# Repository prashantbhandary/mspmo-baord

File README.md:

# MSPM0G3507 Development Board

A compact USB-C development board for TI's **MSPM0G3507** (Arm Cortex-M0+,
80 MHz, 128 KB flash, 32 KB SRAM), with an on-board USB-to-UART bridge, a
3-axis accelerometer and a Tag-Connect SWD footprint.

Full write-up: <https://bhandari-prashant.com.np/projects/mspm0-board>

## At a glance

| | |
| --- | --- |
| Size | 53 × 28 mm, 2-layer, 1.6 mm FR-4, 4 × M3 holes, fiducials |
| Power | USB-C (5.1 kΩ CC pull-downs) → SPX3819 3.3 V LDO |
| USB | CH340E USB-UART on UART0, with RTS/CTS; USBLC6-2SC6 ESD protection |
| Sensor | LIS2DH accelerometer on I²C0, INT1/INT2 to the MCU |
| Clock | 8 MHz crystal on HFXIN/HFXOUT; 100 kΩ on ROSC |
| Debug | SWD + NRST on a TC2030 Tag-Connect footprint (no header) |

## MCU pin map

| Signal | MSPM0 pin | Goes to |
| --- | --- | --- |
| UART0 TX / RX | PA0 / PA1 | CH340E RXD / TXD |
| UART0 RTS / CTS | PA8 / PA9 | CH340E CTS / RTS |
| I²C0 SDA / SCL | PA10 / PA11 | LIS2DH |
| INT1 / INT2 | PB8 / PB9 | LIS2DH interrupts |
| SWDIO / SWCLK | PA19 / PA20 | TC2030 |
| HFXIN / HFXOUT | PA5 / PA6 | 8 MHz crystal |
| ROSC | PA2 | 100 kΩ to GND |

## Project files

```
mspmo-baord/
├── mspmo-baord.kicad_pro   open this in KiCad
├── mspmo-baord.kicad_sch   schematic
├── mspmo-baord.kicad_pcb   layout
├── MSPM0.kicad_sym         custom MCU symbol (referenced by sym-lib-table)
├── bom/ibom.html           interactive BOM, open in a browser
├── fab/
│   ├── mfr/                Gerbers + drill files
│   ├── mspmo-baord.csv     BOM with LCSC part numbers
│   └── posfile/            pick-and-place positions
├── mfr.zip                 fab/mfr zipped for upload
└── images/                 renders used in this README
```

## Ordering

Upload `mfr.zip` to the board house. For assembly, use `fab/mspmo-baord.csv`
(BOM) and `fab/posfile/mspmo-baord-all-pos.csv` (CPL).

## Tools

KiCad 10. Renders made with `kicad-cli pcb render`.

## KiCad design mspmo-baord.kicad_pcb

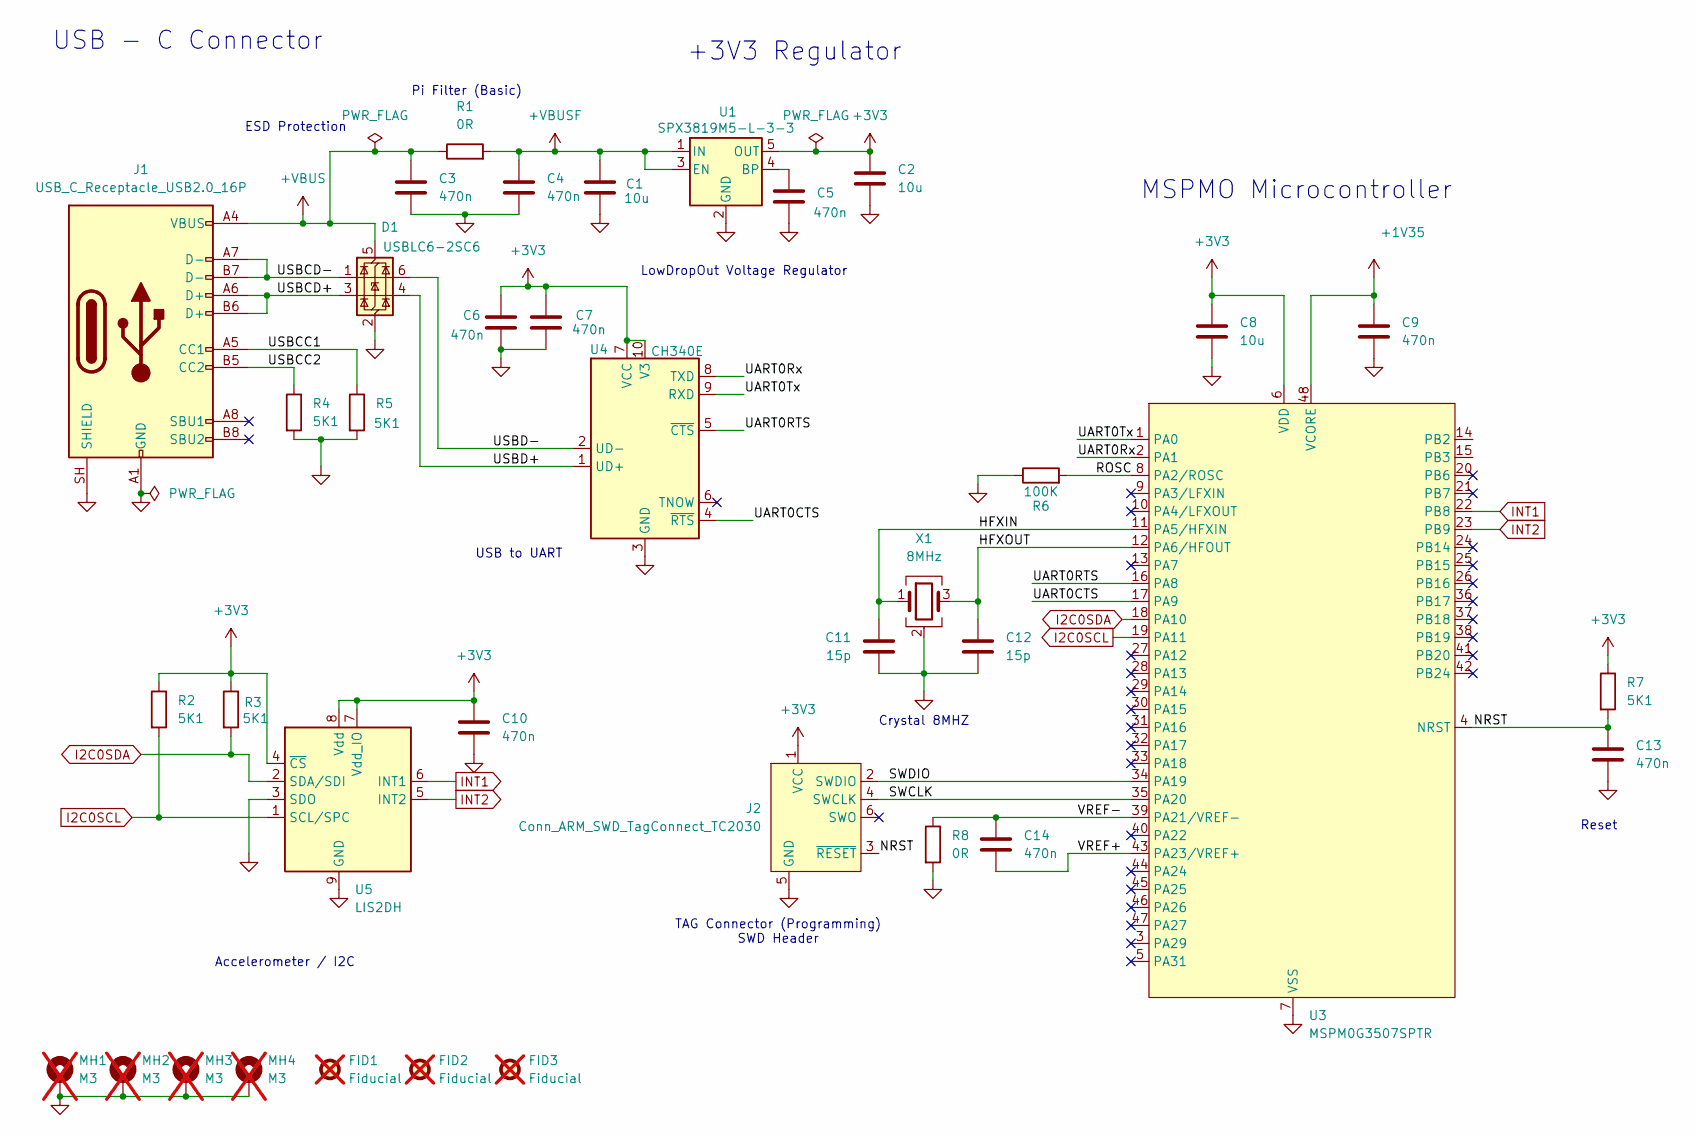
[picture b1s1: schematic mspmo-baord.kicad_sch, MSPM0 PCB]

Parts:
C1, C2, C8: 10u; C_0805_2012Metric; Manufacture Part Number CL21A106KAYNNNE; LCSC C15850
C3, C4, C5, C6, C7, C9, C10, C13, C14: 470n; C_0603_1608Metric; Manufacture Part Number CC0603KRX7R9BB474; LCSC C513577
C11, C12: 15p; C_0603_1608Metric; Manufacture Part Number CC0603KRX7R9BB474; LCSC C513577
D1: USBLC6-2SC6; SOT-23-6
FID1, FID2, FID3: Fiducial; Fiducial_1mm_Mask2mm; not fitted
J1: USB_C_Receptacle_USB2.0_16P; USB_C_Receptacle_GCT_USB4105-xx-A_16P_TopMnt_Horizontal
J2: Conn_ARM_SWD_TagConnect_TC2030; Tag-Connect_TC2030-IDC-FP_2x03_P1.27mm_Vertical
MH1, MH2, MH3, MH4: M3; MountingHole_3.2mm_M3_Pad_Via; not fitted
R1, R8: 0R; R_0603_1608Metric
R2, R3, R4, R5, R7: 5K1; R_0603_1608Metric
R6: 100K; R_0603_1608Metric; Manufacture Part Number RS73F1JTTD1003B; LCSC C4118779
U1: SPX3819M5-L-3-3; SOT-23-5
U3: MSPM0G3507SPTR; LQFP-48_7x7mm_P0.5mm; Manufacture Part Number MSPM0G3507SPTR; LCSC C22362630
U4: CH340E; MSOP-10_3x3mm_P0.5mm
U5: LIS2DH; LGA-14_2x2mm_P0.35mm_LayoutBorder3x4y
X1: 8MHz; Crystal_SMD_3225-4Pin_3.2x2.5mm

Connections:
+1V35: C9.1, U3.48 (VCORE)
+3V3: C2.2, C6.1, C7.1, C8.2, C10.1, J2.1 (VCC), R2.1, R3.1, R7.1, U1.5 (OUT), U3.6 (VDD), U4.7 (VCC), U4.10 (V3), U5.4 (~CS), U5.7 (Vdd_IO), U5.8 (Vdd)
+VBUS: C3.1, D1.5 (VBUS), J1.A4 (VBUS), J1.A9 (VBUS), J1.B4 (VBUS), J1.B9 (VBUS), R1.1
+VBUSF: C1.2, C4.1, R1.2, U1.1 (IN), U1.3 (EN)
/HFXIN: C11.1, U3.11 (PA5/HFXIN), X1.1
/HFXOUT: C12.1, U3.12 (PA6/HFOUT), X1.3
/NRST: C13.1, J2.3 (~RESET), R7.2, U3.4 (NRST)
/ROSC: R6.2, U3.8 (PA2/ROSC)
/SWCLK: J2.4 (SWCLK), U3.35 (PA20)
/SWDIO: J2.2 (SWDIO), U3.34 (PA19)
/UART0CTS: U3.17 (PA9), U4.4 (~RTS)
/UART0RTS: U3.16 (PA8), U4.5 (~CTS)
/UART0Rx: U3.2 (PA1), U4.8 (TXD)
/UART0Tx: U3.1 (PA0), U4.9 (RXD)
/USBCC1: J1.A5 (CC1), R5.1
/USBCC2: J1.B5 (CC2), R4.1
/USBCD+: D1.3 (I/O2), J1.A6 (D+), J1.B6 (D+)
/USBCD-: D1.1 (I/O1), J1.A7 (D-), J1.B7 (D-)
/USBD+: D1.4 (I/O2), U4.1 (UD+)
/USBD-: D1.6 (I/O1), U4.2 (UD-)
/VREF+: C14.2, U3.43 (PA23/VREF+)
/VREF-: C14.1, R8.1, U3.39 (PA21/VREF-)
GND: C1.1, C2.1, C3.2, C4.2, C5.2, C6.2, C7.2, C8.1, C9.2, C10.2, C11.2, C12.2, C13.2, D1.2 (GND), J1.A1 (GND), J1.A12 (GND), J1.B1 (GND), J1.B12 (GND), J1.SH (SHIELD), J2.5 (GND), MH1.1 (1_1), MH2.1 (1_1), MH3.1 (1_1), MH4.1 (1_1), R4.2, R5.2, R6.1, R8.2, U1.2 (GND), U3.7 (VSS), U4.3 (GND), U5.3 (SDO), U5.9 (GND), U5.10 (GND), U5.11 (GND), U5.12 (GND), U5.13 (GND), U5.14 (GND), X1.2 (G), X1.4 (G)
I2C0SCL: R2.2, U3.19 (PA11), U5.1 (SCL/SPC)
I2C0SDA: R3.2, U3.18 (PA10), U5.2 (SDA/SDI)
INT1: U3.22 (PB8), U5.6 (INT1)
INT2: U3.23 (PB9), U5.5 (INT2)
unnamed: C5.1, U1.4 (BP)

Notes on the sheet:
ESD Protection
MSPMO Microcontroller
Crystal 8MHZ
Accelerometer / I2C
Reset
TAG Connector (Programming) SWD Header
+3V3 Regulator
LowDropOut Voltage Regulator
USB to UART
Pi Filter (Basic)
USB - C Connector

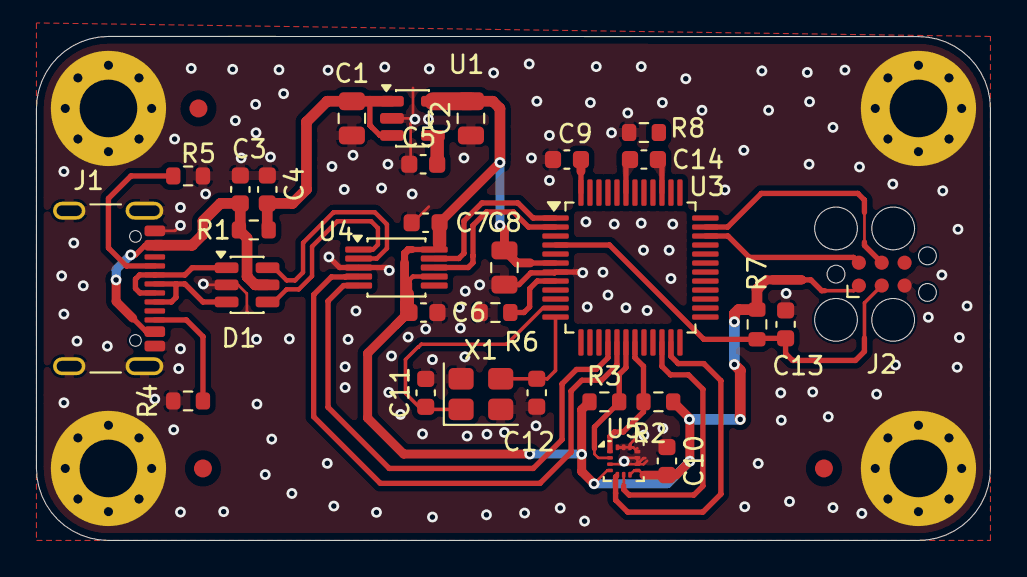
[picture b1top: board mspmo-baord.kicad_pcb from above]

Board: 2 copper layers, 53.0 x 28.0 mm, 37 parts (0 on the bottom side), 28 nets.
